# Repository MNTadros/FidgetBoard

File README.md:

# FidgetBoard

A simple PCB made for fidgeting, introducing the **FidgetBoard v1.0**!  
This project combines tactile fun with basic electronics and serves as a great beginner-friendly hardware build.

## 🔧 Structure

- `FIRMWARE/` — Arduino source code to control the board  
- `PCB/` — PCB design files including drill and Gerber files  
- `PROD/` — Production-ready files, including the Bill of Materials (BOM)  
- `DOCS/` — A browsable website-style documentation for the project

## 🌐 Live Docs

Check out the full live documentation (images, model viewer, BOM, and more) [here](https://mntadros.github.io/FidgetBoard/DOCS/).

## 💡 Version

- **FidgetBoard v1.0**

## 📷 Preview

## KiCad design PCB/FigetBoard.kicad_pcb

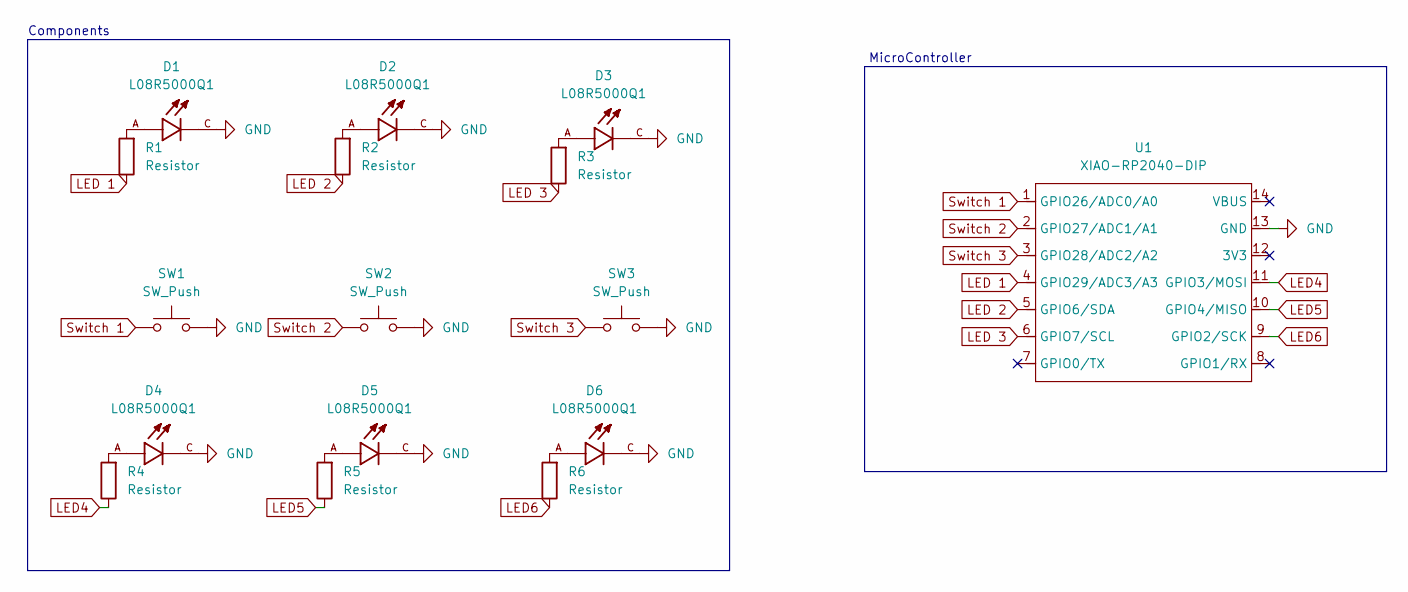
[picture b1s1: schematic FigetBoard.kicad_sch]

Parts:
D1, D2, D3, D4, D5, D6: L08R5000Q1; LEDRD254W57D500H1070; PARTREV NA
R1, R2, R3, R4, R5, R6: Resistor; R_Axial_DIN0204_L3.6mm_D1.6mm_P5.08mm_Horizontal
SW1, SW2, SW3: SW_Push; SW_Cherry_MX_1.00u_PCB
U1: XIAO-RP2040-DIP

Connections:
GND: D1.C, D2.C, D3.C, D4.C, D5.C, D6.C, SW1.2, SW2.2, SW3.2, U1.13 (GND)
LED4: R4.1, U1.11 (GPIO3/MOSI)
LED5: R5.1, U1.10 (GPIO4/MISO)
LED6: R6.1, U1.9 (GPIO2/SCK)
LED 1: R1.1, U1.4 (GPIO29/ADC3/A3)
LED 2: R2.1, U1.5 (GPIO6/SDA)
LED 3: R3.1, U1.6 (GPIO7/SCL)
unnamed: D1.A, R1.2
unnamed: D2.A, R2.2
unnamed: D3.A, R3.2
unnamed: D4.A, R4.2
unnamed: D5.A, R5.2
unnamed: D6.A, R6.2
Switch 1: SW1.1, U1.1 (GPIO26/ADC0/A0)
Switch 2: SW2.1, U1.2 (GPIO27/ADC1/A1)
Switch 3: SW3.1, U1.3 (GPIO28/ADC2/A2)

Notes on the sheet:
Components
MicroController

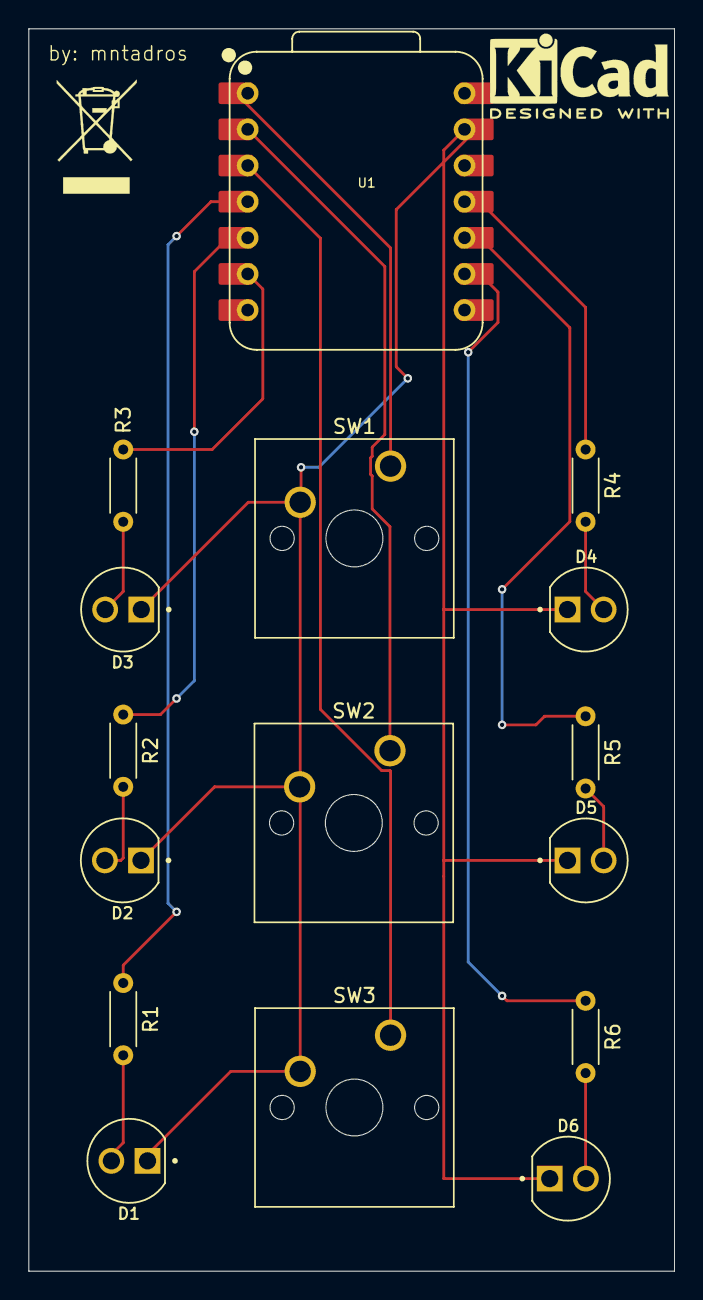
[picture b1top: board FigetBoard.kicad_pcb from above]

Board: 2 copper layers, 45.4 x 87.3 mm, 16 parts (0 on the bottom side), 16 nets.

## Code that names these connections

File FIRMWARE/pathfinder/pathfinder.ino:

int BUT1 = 0;
int BUT2 = 1;
int BUT3 = 2;

int LED1 = 3;
int LED2 = 4;
int LED3 = 5;
int LED4 = 10;
int LED5 = 9;
int LED6 = 8;

int fadeValue = 0;
int fadeAmount = 5;
unsigned long previousMillis = 0;
const long interval = 30;

void setup() {
  // All of the Cherry MX Switches are inputs
  pinMode(BUT1, INPUT);
  pinMode(BUT2, INPUT);
  pinMode(BUT3, INPUT);

  // All of the LEDs are outputs
  pinMode(LED1, OUTPUT);
  pinMode(LED2, OUTPUT);
  pinMode(LED3, OUTPUT);
  pinMode(LED4, OUTPUT);
  pinMode(LED5, OUTPUT);
  pinMode(LED6, OUTPUT);
}

void loop() {
  bool b1 = digitalRead(BUT1);
  bool b2 = digitalRead(BUT2);
  bool b3 = digitalRead(BUT3);

  if (b1) {
    // BUTTON 1: All LEDs ON
    digitalWrite(LED1, HIGH);
    digitalWrite(LED2, HIGH);
    digitalWrite(LED3, HIGH);
    digitalWrite(LED4, HIGH);
    digitalWrite(LED5, HIGH);
    digitalWrite(LED6, HIGH);
  }
  else if (b2) {
    // BUTTON 2: Cycle LEDs 1-3 ON, 4-6 OFF and toggle on interval
    static unsigned long lastToggle = 0;
    static bool state = false;
    if (millis() - lastToggle >= 500) {
      lastToggle = millis();
      state = !state;
      digitalWrite(LED1, state);
      digitalWrite(LED2, state);
      digitalWrite(LED3, state);
      digitalWrite(LED4, !state);
      digitalWrite(LED5, !state);
      digitalWrite(LED6, !state);
    }
  }
  else if (b3) {
    // BUTTON 3: Alternate LED pattern toggle
    static unsigned long lastToggle = 0;
    static bool state = false;
    if (millis() - lastToggle >= 500) {
      lastToggle = millis();
      state = !state;
      digitalWrite(LED1, state);
      digitalWrite(LED2, !state);
      digitalWrite(LED3, state);
      digitalWrite(LED4, !state);
      digitalWrite(LED5, state);
      digitalWrite(LED6, state);
    }
  }
  else {
    // DEFAULT: All LEDs fade in and out together
    unsigned long currentMillis = millis();
    if (currentMillis - previousMillis >= interval) {
      previousMillis = currentMillis;
      analogWrite(LED1, fadeValue);
      analogWrite(LED2, fadeValue);
      analogWrite(LED3, fadeValue);
      analogWrite(LED4, fadeValue);
      analogWrite(LED5, fadeValue);
      analogWrite(LED6, fadeValue);

      fadeValue += fadeAmount;
      if (fadeValue <= 0 || fadeValue >= 255) {
        fadeAmount = -fadeAmount;
      }
    }
  }
}

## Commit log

2025-07-05 initial file upload
2025-07-05 updated where imgs get pulled from
2025-07-05 edited README
2025-07-05 fixed 3d model view on the website
2025-07-05 updated Docs link in readme
2025-07-05 fixed mission favicon on docs
2025-07-05 wrong vendor name
